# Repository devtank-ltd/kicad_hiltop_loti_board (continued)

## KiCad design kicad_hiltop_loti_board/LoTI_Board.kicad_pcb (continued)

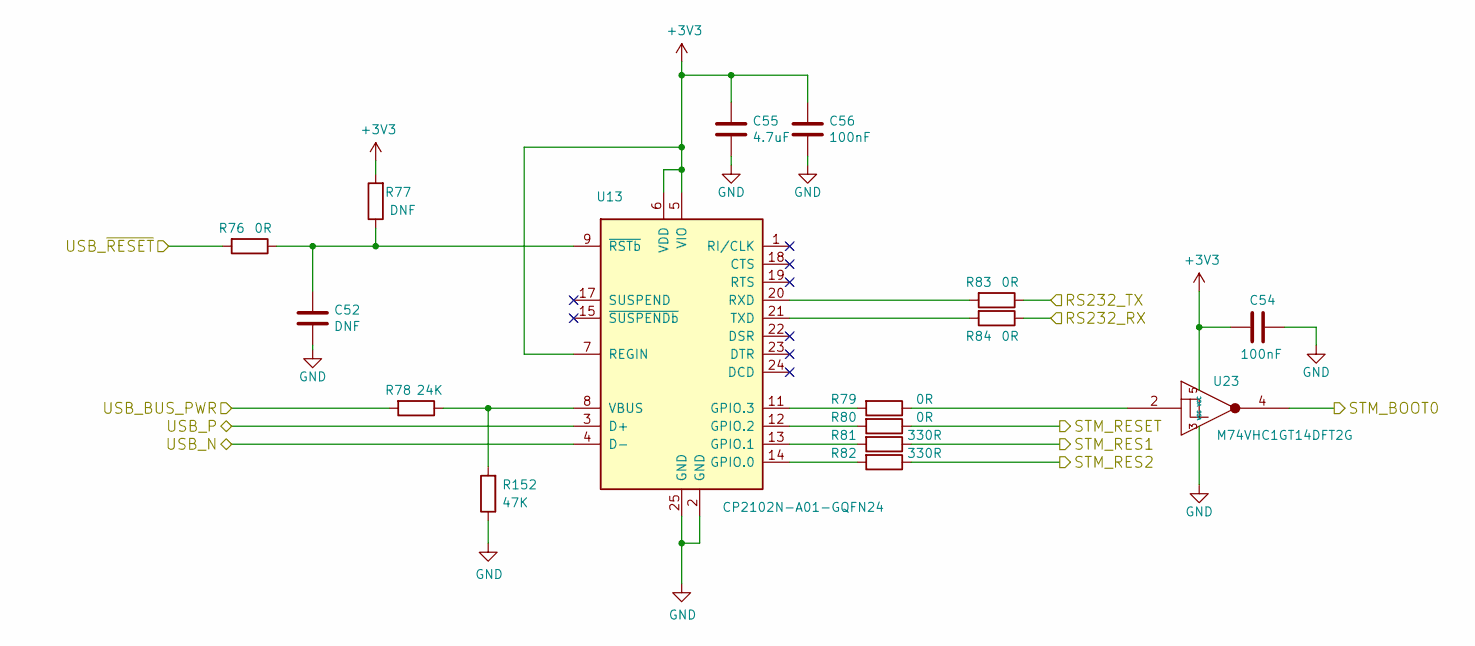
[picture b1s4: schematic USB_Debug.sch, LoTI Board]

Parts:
C52: DNF; C_0603_1608Metric
C54, C56: 100nF; C_0603_1608Metric
C55: 4.7uF; C_0805_2012Metric
R76, R79, R80, R83, R84: 0R; R_0603_1608Metric
R77: DNF; R_0603_1608Metric
R78: 24K; R_0603_1608Metric
R81, R82: 330R; R_0603_1608Metric
R152: 47K; R_0603_1608Metric
U13: CP2102N-A01-GQFN24; QFN-24-1EP_4x4mm_P0.5mm_EP2.6x2.6mm_ThermalVias
U23: M74VHC1GT14DFT2G; SOT-353_SC-70-5

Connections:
+3V3: C54.2, C55.1, C56.1, R77.2, U13.5 (VIO), U13.6 (VDD), U13.7 (REGIN), U23.5 (VCC); also elsewhere on the board
+5V: R78.2; also elsewhere on the board
/RESET: R76.2; also elsewhere on the board
/STM_BOOT0: U23.4; also elsewhere on the board
/STM_DEBUG_RX: R84.1; also elsewhere on the board
/STM_DEBUG_TX: R83.1; also elsewhere on the board
/STM_RES1: R81.1; also elsewhere on the board
/STM_RES2: R82.1; also elsewhere on the board
/STM_RESET: R80.1; also elsewhere on the board
/USB_DEBUG_N: U13.4 (D-); also elsewhere on the board
/USB_DEBUG_P: U13.3 (D+); also elsewhere on the board
GND: C52.2, C54.1, C55.2, C56.2, R152.1, U13.2 (GND), U13.25 (GND), U23.3 (VSS); also elsewhere on the board
unnamed: C52.1, R76.1, R77.1, U13.9 (~RSTb)
unnamed: R79.1, U23.2
unnamed: R79.2, U13.11 (GPIO.3)
unnamed: R80.2, U13.12 (GPIO.2)
unnamed: R81.2, U13.13 (GPIO.1)
unnamed: R82.2, U13.14 (GPIO.0)
unnamed: R83.2, U13.20 (RXD)
unnamed: R84.2, U13.21 (TXD)
unnamed: R78.1, R152.2, U13.8 (VBUS)

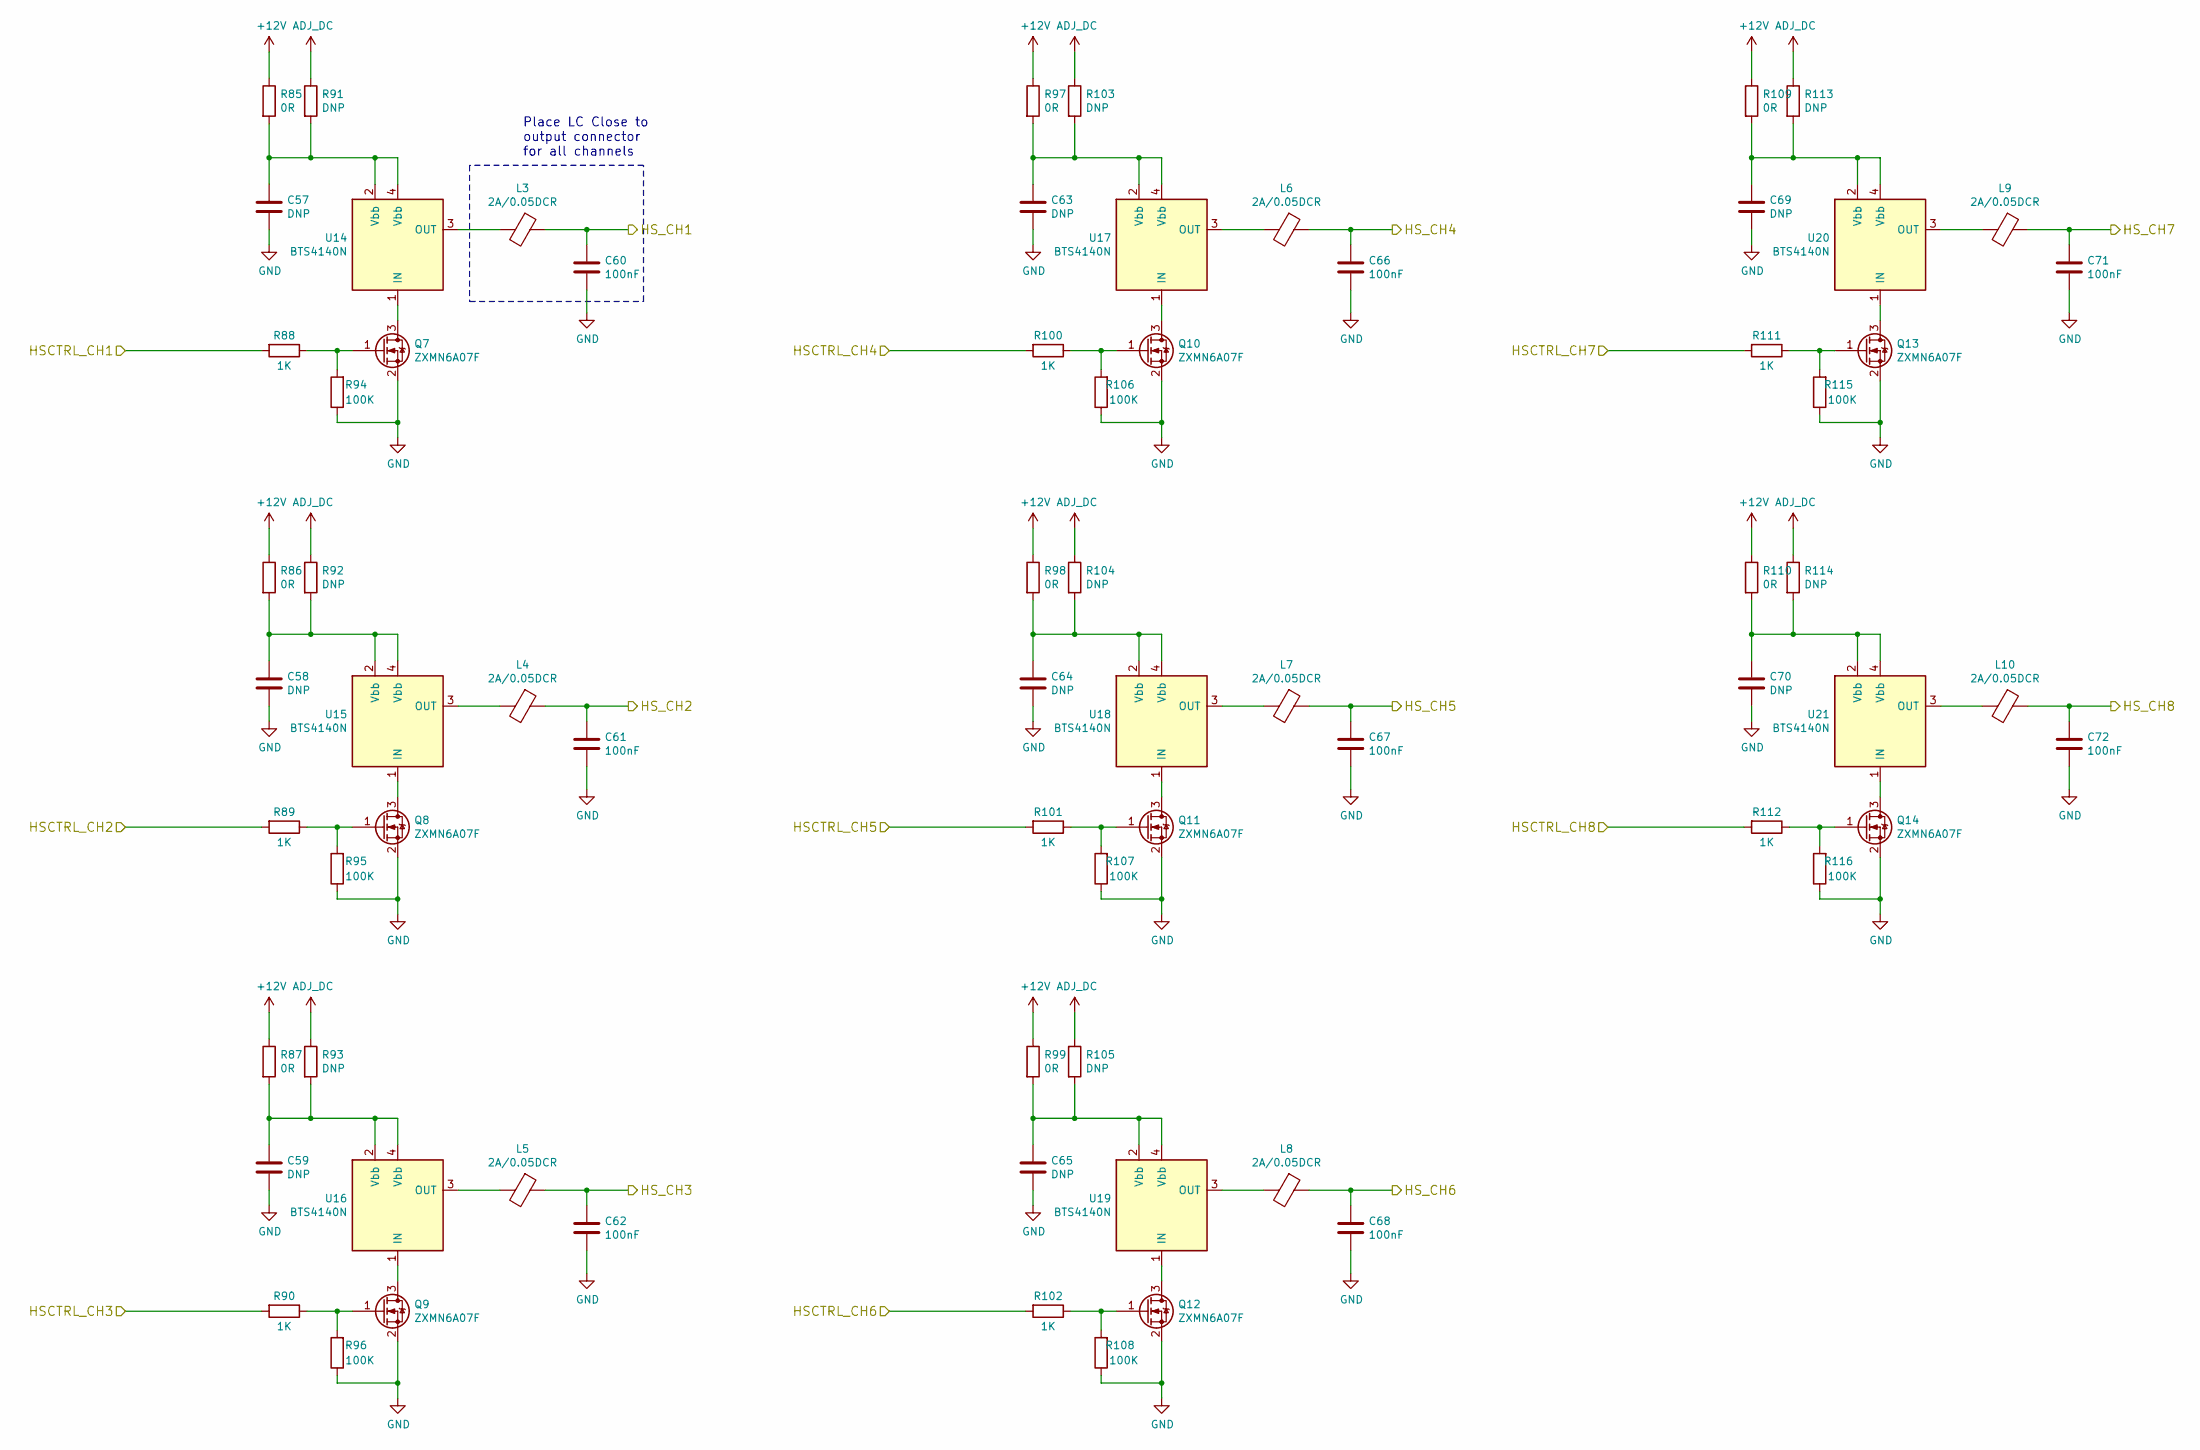
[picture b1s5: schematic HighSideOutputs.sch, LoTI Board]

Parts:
C57, C58, C59, C63, C64, C65, C69, C70: DNP; C_0805_2012Metric
C60, C61, C62, C66, C67, C68, C71, C72: 100nF; C_0402_1005Metric
L3, L4, L5, L6, L7, L8, L9, L10: 2A/0.05DCR; L_0805_2012Metric
Q7, Q8, Q9, Q10, Q11, Q12, Q13, Q14: ZXMN6A07F; SOT-23
R85, R86, R87, R97, R98, R99, R109, R110: 0R; R_0805_2012Metric
R88, R89, R90, R100, R101, R102, R111, R112: 1K; R_0603_1608Metric
R91, R92, R93, R103, R104, R105, R113, R114: DNP; R_0805_2012Metric
R94, R95, R96, R106, R107, R108, R115, R116: 100K; R_0603_1608Metric
U14, U15, U16, U17, U18, U19, U20, U21: BTS4140N; SOT-223

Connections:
+12V: R85.1, R86.1, R87.1, R97.1, R98.1, R99.1, R109.1, R110.1; also elsewhere on the board
/HS_CTRL_SW1: R88.2; also elsewhere on the board
/HS_CTRL_SW2: R89.2; also elsewhere on the board
/HS_CTRL_SW3: R90.2; also elsewhere on the board
/HS_CTRL_SW4: R100.2; also elsewhere on the board
/HS_CTRL_SW5: R101.2; also elsewhere on the board
/HS_CTRL_SW6: R102.2; also elsewhere on the board
/HS_CTRL_SW7: R111.2; also elsewhere on the board
/HS_CTRL_SW8: R112.2; also elsewhere on the board
/HS_OUT1: C60.1, L3.1; also elsewhere on the board
/HS_OUT2: C61.1, L4.1; also elsewhere on the board
/HS_OUT3: C62.1, L5.1; also elsewhere on the board
/HS_OUT4: C66.1, L6.1; also elsewhere on the board
/HS_OUT5: C67.1, L7.1; also elsewhere on the board
/HS_OUT6: C68.1, L8.1; also elsewhere on the board
/HS_OUT7: C71.1, L9.1; also elsewhere on the board
/HS_OUT8: C72.1, L10.1; also elsewhere on the board
ADJ_DC: R91.1, R92.1, R93.1, R103.1, R104.1, R105.1, R113.1, R114.1; also elsewhere on the board
GND: C57.2, C58.2, C59.2, C60.2, C61.2, C62.2, C63.2, C64.2, C65.2, C66.2, C67.2, C68.2, C69.2, C70.2, C71.2, C72.2, Q7.2 (S), Q8.2 (S), Q9.2 (S), Q10.2 (S), Q11.2 (S), Q12.2 (S), Q13.2 (S), Q14.2 (S), R94.1, R95.1, R96.1, R106.1, R107.1, R108.1, R115.1, R116.1; also elsewhere on the board
unnamed: C57.1, R85.2, R91.2, U14.2 (Vbb), U14.4 (Vbb)
unnamed: C58.1, R86.2, R92.2, U15.2 (Vbb), U15.4 (Vbb)
unnamed: C59.1, R87.2, R93.2, U16.2 (Vbb), U16.4 (Vbb)
unnamed: C63.1, R97.2, R103.2, U17.2 (Vbb), U17.4 (Vbb)
unnamed: C64.1, R98.2, R104.2, U18.2 (Vbb), U18.4 (Vbb)
unnamed: C65.1, R99.2, R105.2, U19.2 (Vbb), U19.4 (Vbb)
unnamed: C69.1, R109.2, R113.2, U20.2 (Vbb), U20.4 (Vbb)
unnamed: C70.1, R110.2, R114.2, U21.2 (Vbb), U21.4 (Vbb)
unnamed: L3.2, U14.3 (OUT)
unnamed: L4.2, U15.3 (OUT)
unnamed: L5.2, U16.3 (OUT)
unnamed: L6.2, U17.3 (OUT)
unnamed: L7.2, U18.3 (OUT)
unnamed: L8.2, U19.3 (OUT)
unnamed: L9.2, U20.3 (OUT)
unnamed: L10.2, U21.3 (OUT)
unnamed: Q7.1 (G), R88.1, R94.2
unnamed: Q7.3 (D), U14.1 (IN)
unnamed: Q8.1 (G), R89.1, R95.2
unnamed: Q8.3 (D), U15.1 (IN)
unnamed: Q9.1 (G), R90.1, R96.2
unnamed: Q9.3 (D), U16.1 (IN)
unnamed: Q10.1 (G), R100.1, R106.2
unnamed: Q10.3 (D), U17.1 (IN)
unnamed: Q11.1 (G), R101.1, R107.2
unnamed: Q11.3 (D), U18.1 (IN)
unnamed: Q12.1 (G), R102.1, R108.2
unnamed: Q12.3 (D), U19.1 (IN)
unnamed: Q13.1 (G), R111.1, R115.2
unnamed: Q13.3 (D), U20.1 (IN)
unnamed: Q14.1 (G), R112.1, R116.2
unnamed: Q14.3 (D), U21.1 (IN)

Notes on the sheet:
Place LC Close to output connector for all channels

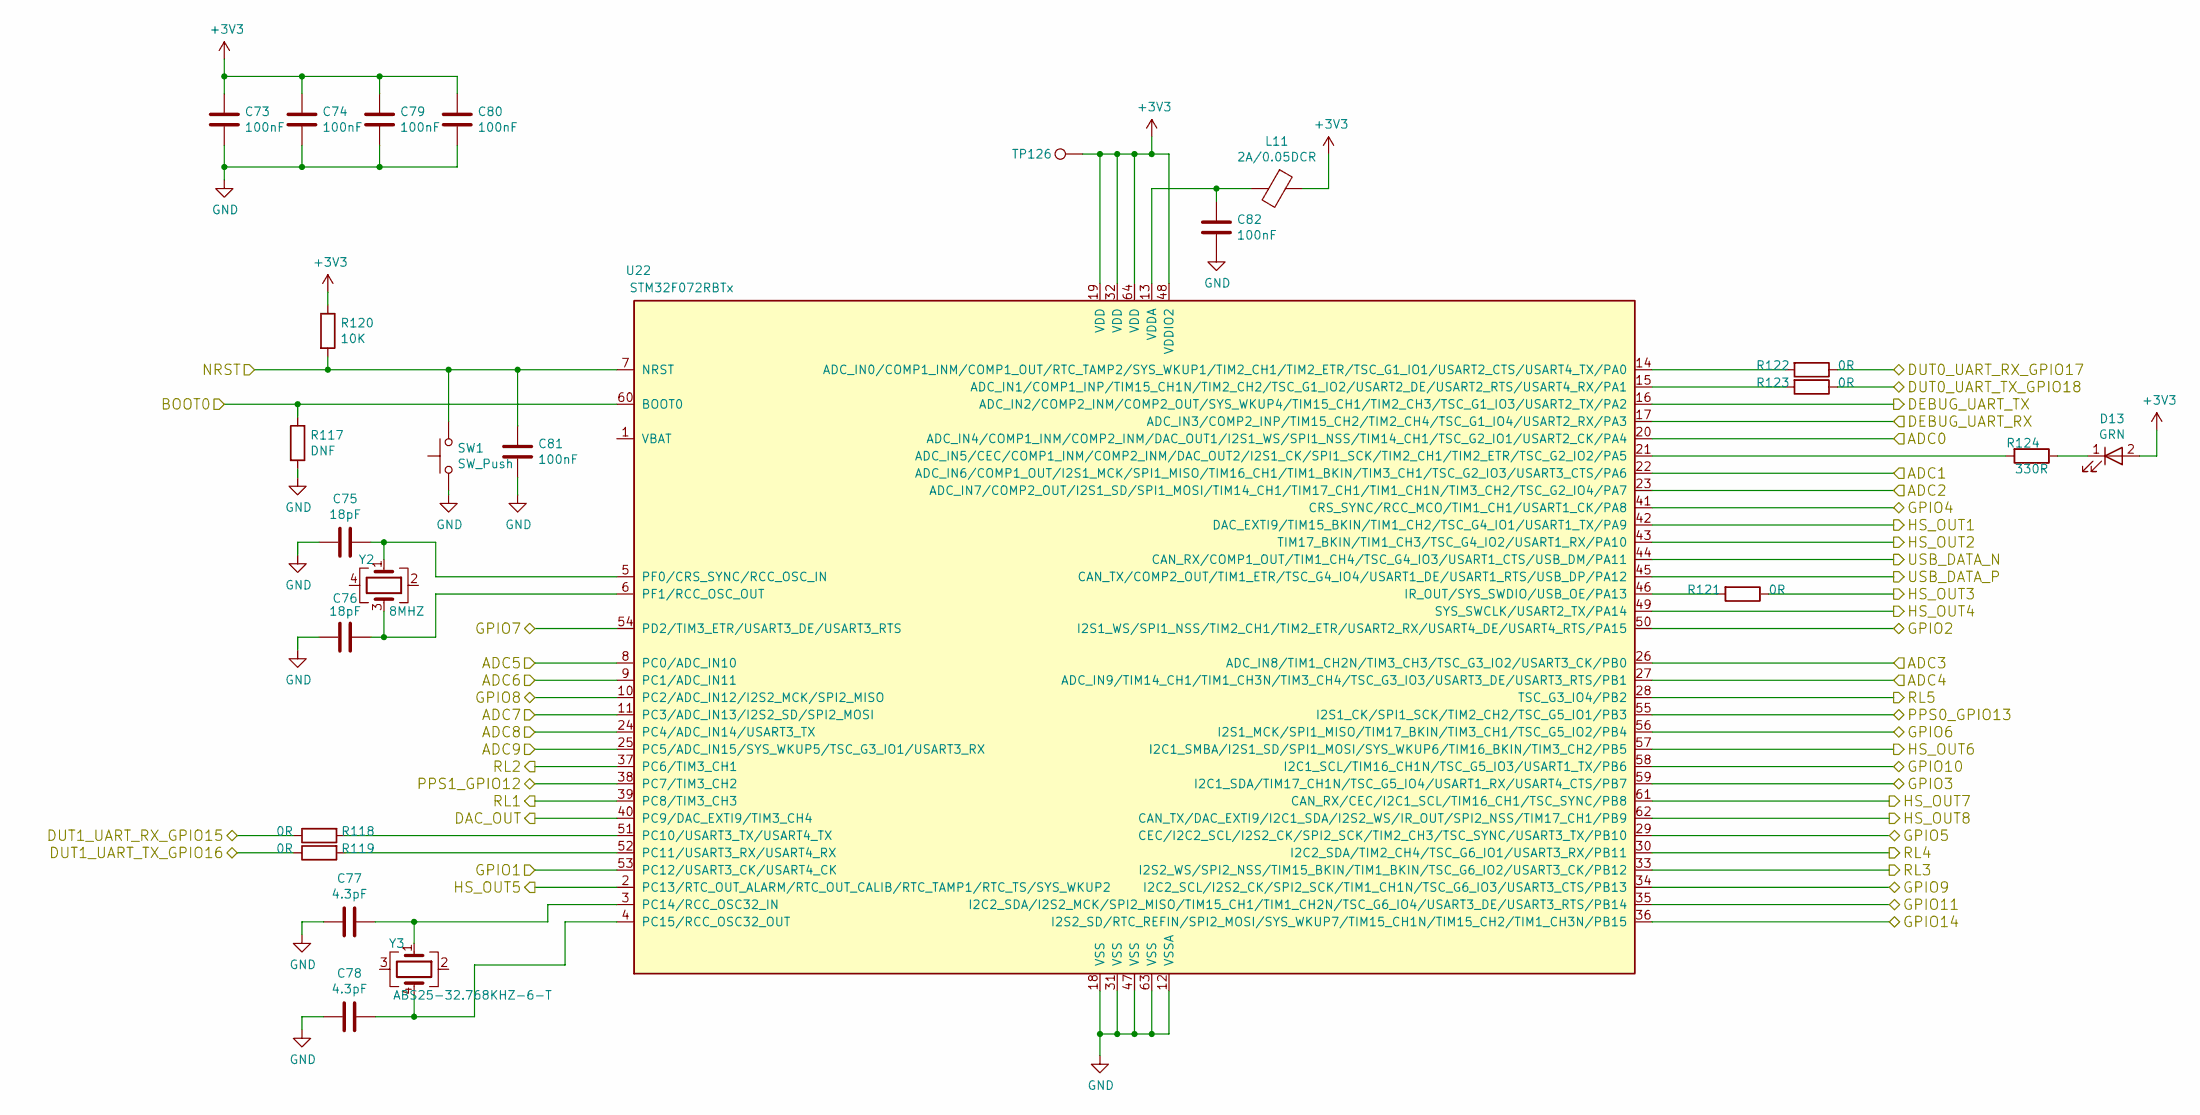
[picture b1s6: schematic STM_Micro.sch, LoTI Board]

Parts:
C73, C74, C79, C80, C81, C82: 100nF; C_0603_1608Metric
C75, C76: 18pF; C_0603_1608Metric
C77, C78: 4.3pF; C_0603_1608Metric
D13: GRN; LED_0603_1608Metric
L11: 2A/0.05DCR; L_0805_2012Metric
R117: DNF; R_0603_1608Metric
R118, R119, R121, R122, R123: 0R; R_0603_1608Metric
R120: 10K; R_0603_1608Metric
R124: 330R; R_0603_1608Metric
SW1: SW_Push; SW_SPST_B3U-1000P
TP126: Test_Point; TestPoint_THTPad_D1.0mm_Drill0.5mm
U22: STM32F072RBTx; LQFP-64_10x10mm_P0.5mm
Y2: 8MHZ; Crystal_SMD_Abracon_ABM3C-4Pin_5.0x3.2mm
Y3: ABS25-32.768KHZ-6-T; Crystal_SMD_7050-4Pin_7.0x5.0mm

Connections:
+3V3: C73.1, C74.1, C79.1, C80.1, D13.2 (A), L11.1, R120.1, TP126.1, U22.19 (VDD), U22.32 (VDD), U22.48 (VDDIO2), U22.64 (VDD); also elsewhere on the board
/ADC0: U22.20 (ADC_IN4/COMP1_INM/COMP2_INM/DAC_OUT1/I2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); also elsewhere on the board
/ADC1: U22.22 (ADC_IN6/COMP1_OUT/I2S1_MCK/SPI1_MISO/TI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); also elsewhere on the board
/ADC2: U22.23 (ADC_IN7/COMP2_OUT/I2S1_SD/SPI1_MOSI/TIM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); also elsewhere on the board
/ADC3: U22.26 (ADC_IN8/TIM1_CH2N/TIM3_CH3/TSC_G3_IO2/U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); also elsewhere on the board
/ADC4: U22.27 (ADC_IN9/TIM14_CH1/TIM1_CH3N/TIM3_CH4/TS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); also elsewhere on the board
/ADC5: U22.8 (PC0/ADC_IN10); also elsewhere on the board
/ADC6: U22.9 (PC1/ADC_IN11); also elsewhere on the board
/ADC7: U22.11 (PC3/ADC_IN13/I2S2_SD/SPI2_MOSI); also elsewhere on the board
/ADC8: U22.24 (PC4/ADC_IN14/USART3_TX); also elsewhere on the board
/ADC9: U22.25 (PC5/ADC_IN15/SYS_WKUP5/TSC_G3_IO1/USART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); also elsewhere on the board
/DUT0_UART_RX_GPIO17: R122.1; also elsewhere on the board
/DUT0_UART_TX_GPIO18: R123.1; also elsewhere on the board
/DUT1_UART_RX_GPIO15: R118.1; also elsewhere on the board
/DUT1_UART_TX_GPIO16: R119.1; also elsewhere on the board
/GPIO1: U22.53 (PC12/USART3_CK/USART4_CK); also elsewhere on the board
/GPIO2: U22.50 (I2S1_WS/SPI1_NSS/TIM2_CH1/TIM2_ETR/USAR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); also elsewhere on the board
/GPIO3: U22.59 (I2C1_SDA/TIM17_CH1N/TSC_G5_IO4/USART1_R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); also elsewhere on the board
/GPIO4: U22.41 (CRS_SYNC/RCC_MCO/TIM1_CH1/USART1_CK/PA8); also elsewhere on the board
/GPIO5: U22.29 (CEC/I2C2_SCL/I2S2_CK/SPI2_SCK/TIM2_CH3/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); also elsewhere on the board
/GPIO6: U22.56 (I2S1_MCK/SPI1_MISO/TIM17_BKIN/TIM3_CH1/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); also elsewhere on the board
/GPIO7: U22.54 (PD2/TIM3_ETR/USART3_DE/USART3_RTS); also elsewhere on the board
/GPIO8: U22.10 (PC2/ADC_IN12/I2S2_MCK/SPI2_MISO); also elsewhere on the board
/GPIO9: U22.34 (I2C2_SCL/I2S2_CK/SPI2_SCK/TIM1_CH1N/TSC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); also elsewhere on the board
/GPIO10: U22.58 (I2C1_SCL/TIM16_CH1N/TSC_G5_IO3/USART1_T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); also elsewhere on the board
/GPIO11: U22.35 (I2C2_SDA/I2S2_MCK/SPI2_MISO/TIM15_CH1/T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); also elsewhere on the board
/GPIO14: U22.36 (I2S2_SD/RTC_REFIN/SPI2_MOSI/SYS_WKUP7/T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); also elsewhere on the board
/HS_CTRL_SW1: U22.42 (DAC_EXTI9/TIM15_BKIN/TIM1_CH2/TSC_G4_IO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); also elsewhere on the board
/HS_CTRL_SW2: U22.43 (TIM17_BKIN/TIM1_CH3/TSC_G4_IO2/USART1_R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); also elsewhere on the board
/HS_CTRL_SW3: R121.1; also elsewhere on the board
/HS_CTRL_SW4: U22.49 (SYS_SWCLK/USART2_TX/PA14); also elsewhere on the board
/HS_CTRL_SW5: U22.2 (PC13/RTC_OUT_ALARM/RTC_OUT_CALIB/RTC_TA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); also elsewhere on the board
/HS_CTRL_SW6: U22.57 (I2C1_SMBA/I2S1_SD/SPI1_MOSI/SYS_WKUP6/T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); also elsewhere on the board
/HS_CTRL_SW7: U22.61 (CAN_RX/CEC/I2C1_SCL/TIM16_CH1/TSC_SYNC/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); also elsewhere on the board
/HS_CTRL_SW8: U22.62 (CAN_TX/DAC_EXTI9/I2C1_SDA/I2S2_WS/IR_OU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); also elsewhere on the board
/PPS0_GPIO13: U22.55 (I2S1_CK/SPI1_SCK/TIM2_CH2/TSC_G5_IO1/PB3); also elsewhere on the board
/PPS1_GPIO12: U22.38 (PC7/TIM3_CH2); also elsewhere on the board
/RL1_OUT: U22.39 (PC8/TIM3_CH3); also elsewhere on the board
/RL2_OUT: U22.37 (PC6/TIM3_CH1); also elsewhere on the board
/RL3_OUT: U22.33 (I2S2_WS/SPI2_NSS/TIM15_BKIN/TIM1_BKIN/T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); also elsewhere on the board
/RL4_OUT: U22.30 (I2C2_SDA/TIM2_CH4/TSC_G6_IO1/USART3_RX/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); also elsewhere on the board
/RL5_OUT: U22.28 (TSC_G3_IO4/PB2); also elsewhere on the board
/STM_BOOT0: R117.1, U22.60 (BOOT0); also elsewhere on the board
/STM_DEBUG_RX: U22.17 (ADC_IN3/COMP2_INP/TIM15_CH2/TIM2_CH4/TS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); also elsewhere on the board
/STM_DEBUG_TX: U22.16 (ADC_IN2/COMP2_INM/COMP2_OUT/SYS_WKUP4/T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); also elsewhere on the board
/STM_Micro/DAC_OUT: U22.40 (PC9/DAC_EXTI9/TIM3_CH4); also elsewhere on the board
/STM_RESET: C81.1, R120.2, SW1.2, U22.7 (NRST); also elsewhere on the board
/USB_DATA_N: U22.44 (CAN_RX/COMP1_OUT/TIM1_CH4/TSC_G4_IO3/US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); also elsewhere on the board
/USB_DATA_P: U22.45 (CAN_TX/COMP2_OUT/TIM1_ETR/TSC_G4_IO4/US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); also elsewhere on the board
GND: C73.2, C74.2, C75.2, C76.2, C77.2, C78.2, C79.2, C80.2, C81.2, C82.2, R117.2, SW1.1, U22.12 (VSSA), U22.18 (VSS), U22.31 (VSS), U22.47 (VSS), U22.63 (VSS); also elsewhere on the board
unnamed: C75.1, U22.5 (PF0/CRS_SYNC/RCC_OSC_IN), Y2.1
unnamed: C76.1, U22.6 (PF1/RCC_OSC_OUT), Y2.3
unnamed: C77.1, U22.3 (PC14/RCC_OSC32_IN), Y3.1
unnamed: C78.1, U22.4 (PC15/RCC_OSC32_OUT), Y3.4
unnamed: C82.1, L11.2, U22.13 (VDDA)
unnamed: D13.1 (K), R124.1
unnamed: R118.2, U22.51 (PC10/USART3_TX/USART4_TX)
unnamed: R119.2, U22.52 (PC11/USART3_RX/USART4_RX)
unnamed: R121.2, U22.46 (IR_OUT/SYS_SWDIO/USB_OE/PA13)
unnamed: R122.2, U22.14 (ADC_IN0/COMP1_INM/COMP1_OUT/RTC_TAMP2/S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)
unnamed: R123.2, U22.15 (ADC_IN1/COMP1_INP/TIM15_CH1N/TIM2_CH2/T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)
unnamed: R124.2, U22.21 (ADC_IN5/CEC/COMP1_INM/COMP2_INM/DAC_OUT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)

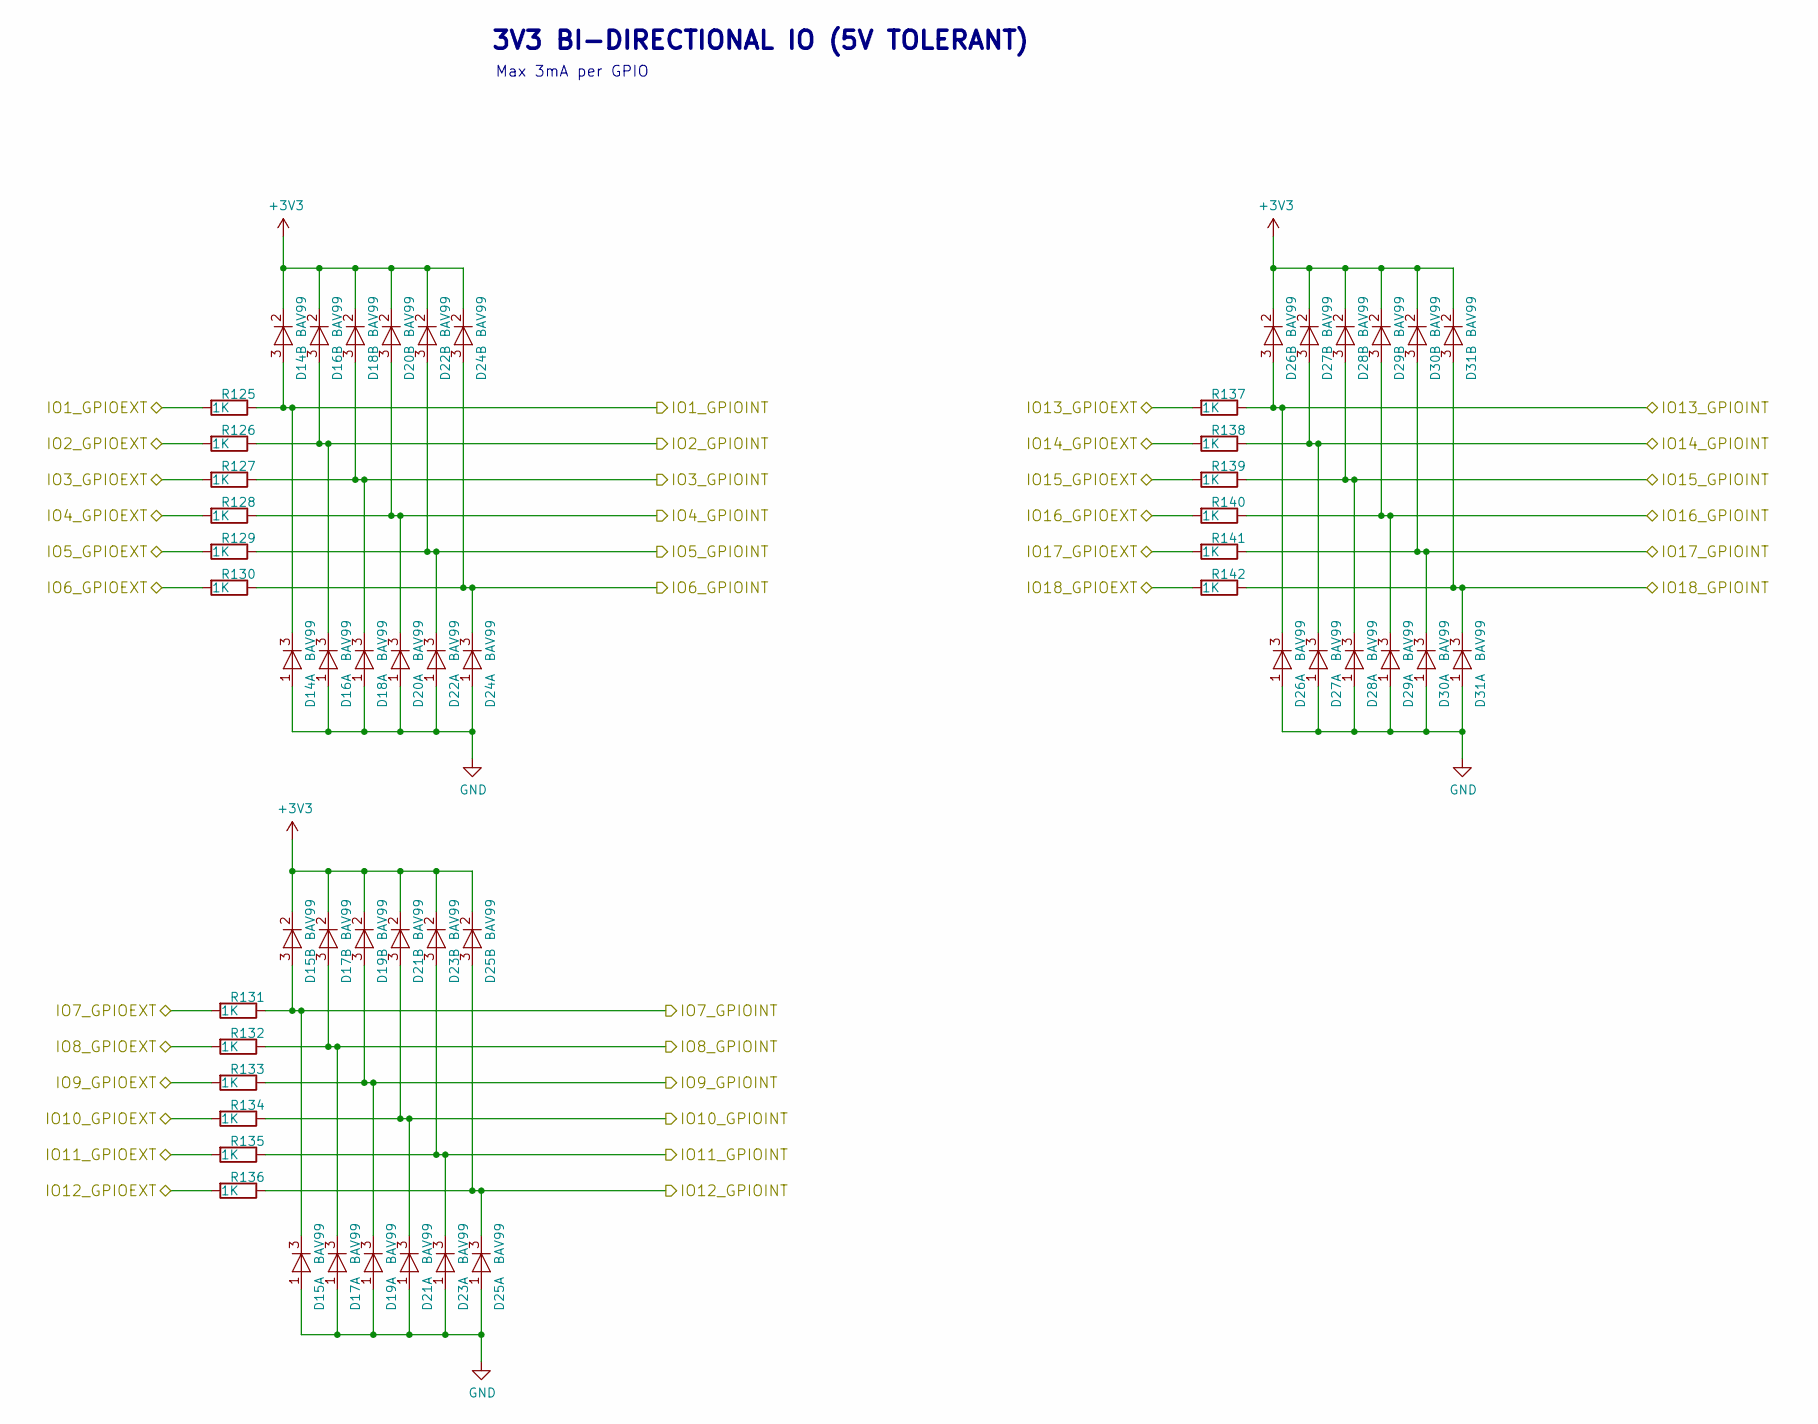
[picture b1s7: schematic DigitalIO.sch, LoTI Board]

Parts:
D14, D15, D16, D17, D18, D19, D20, D21, D22, D23, D24, D25, D26, D27, D28, D29, D30, D31: BAV99; SOT-23
R125, R126, R127, R128, R129, R130, R131, R132, R133, R134, R135, R136, R137, R138, R139, R140, R141, R142: 1K; R_0603_1608Metric

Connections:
+3V3: D14.2 (K), D15.2 (K), D16.2 (K), D17.2 (K), D18.2 (K), D19.2 (K), D20.2 (K), D21.2 (K), D22.2 (K), D23.2 (K), D24.2 (K), D25.2 (K), D26.2 (K), D27.2 (K), D28.2 (K), D29.2 (K), D30.2 (K), D31.2 (K); also elsewhere on the board
/DUT0_RX_GPIO17_EXT: R141.2; also elsewhere on the board
/DUT0_TX_GPIO18_EXT: R142.2; also elsewhere on the board
/DUT0_UART_RX_GPIO17: D30.3 (K), R141.1; also elsewhere on the board
/DUT0_UART_TX_GPIO18: D31.3 (K), R142.1; also elsewhere on the board
/DUT1_RX_GPIO15_EXT: R139.2; also elsewhere on the board
/DUT1_TX_GPIO16_EXT: R140.2; also elsewhere on the board
/DUT1_UART_RX_GPIO15: D28.3 (K), R139.1; also elsewhere on the board
/DUT1_UART_TX_GPIO16: D29.3 (K), R140.1; also elsewhere on the board
/GPIO1: D14.3 (K), R125.1; also elsewhere on the board
/GPIO1_EXT: R125.2; also elsewhere on the board
/GPIO2: D16.3 (K), R126.1; also elsewhere on the board
/GPIO2_EXT: R126.2; also elsewhere on the board
/GPIO3: D18.3 (K), R127.1; also elsewhere on the board
/GPIO3_EXT: R127.2; also elsewhere on the board
/GPIO4: D20.3 (K), R128.1; also elsewhere on the board
/GPIO4_EXT: R128.2; also elsewhere on the board
/GPIO5: D22.3 (K), R129.1; also elsewhere on the board
/GPIO5_EXT: R129.2; also elsewhere on the board
/GPIO6: D24.3 (K), R130.1; also elsewhere on the board
/GPIO6_EXT: R130.2; also elsewhere on the board
/GPIO7: D15.3 (K), R131.1; also elsewhere on the board
/GPIO7_EXT: R131.2; also elsewhere on the board
/GPIO8: D17.3 (K), R132.1; also elsewhere on the board
/GPIO8_EXT: R132.2; also elsewhere on the board
/GPIO9: D19.3 (K), R133.1; also elsewhere on the board
/GPIO9_EXT: R133.2; also elsewhere on the board
/GPIO10: D21.3 (K), R134.1; also elsewhere on the board
/GPIO10_EXT: R134.2; also elsewhere on the board
/GPIO11: D23.3 (K), R135.1; also elsewhere on the board
/GPIO11_EXT: R135.2; also elsewhere on the board
/GPIO14: D27.3 (K), R138.1; also elsewhere on the board
/GPIO14_EXT: R138.2; also elsewhere on the board
/PPS0_GPIO13: D26.3 (K), R137.1; also elsewhere on the board
/PPS0_GPIO13_EXT: R137.2; also elsewhere on the board
/PPS1_GPIO12: D25.3 (K), R136.1; also elsewhere on the board
/PPS1_GPIO12_EXT: R136.2; also elsewhere on the board
GND: D14.1 (A), D15.1 (A), D16.1 (A), D17.1 (A), D18.1 (A), D19.1 (A), D20.1 (A), D21.1 (A), D22.1 (A), D23.1 (A), D24.1 (A), D25.1 (A), D26.1 (A), D27.1 (A), D28.1 (A), D29.1 (A), D30.1 (A), D31.1 (A); also elsewhere on the board

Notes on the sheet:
3V3 BI-DIRECTIONAL IO (5V TOLERANT)
Max 3mA per GPIO

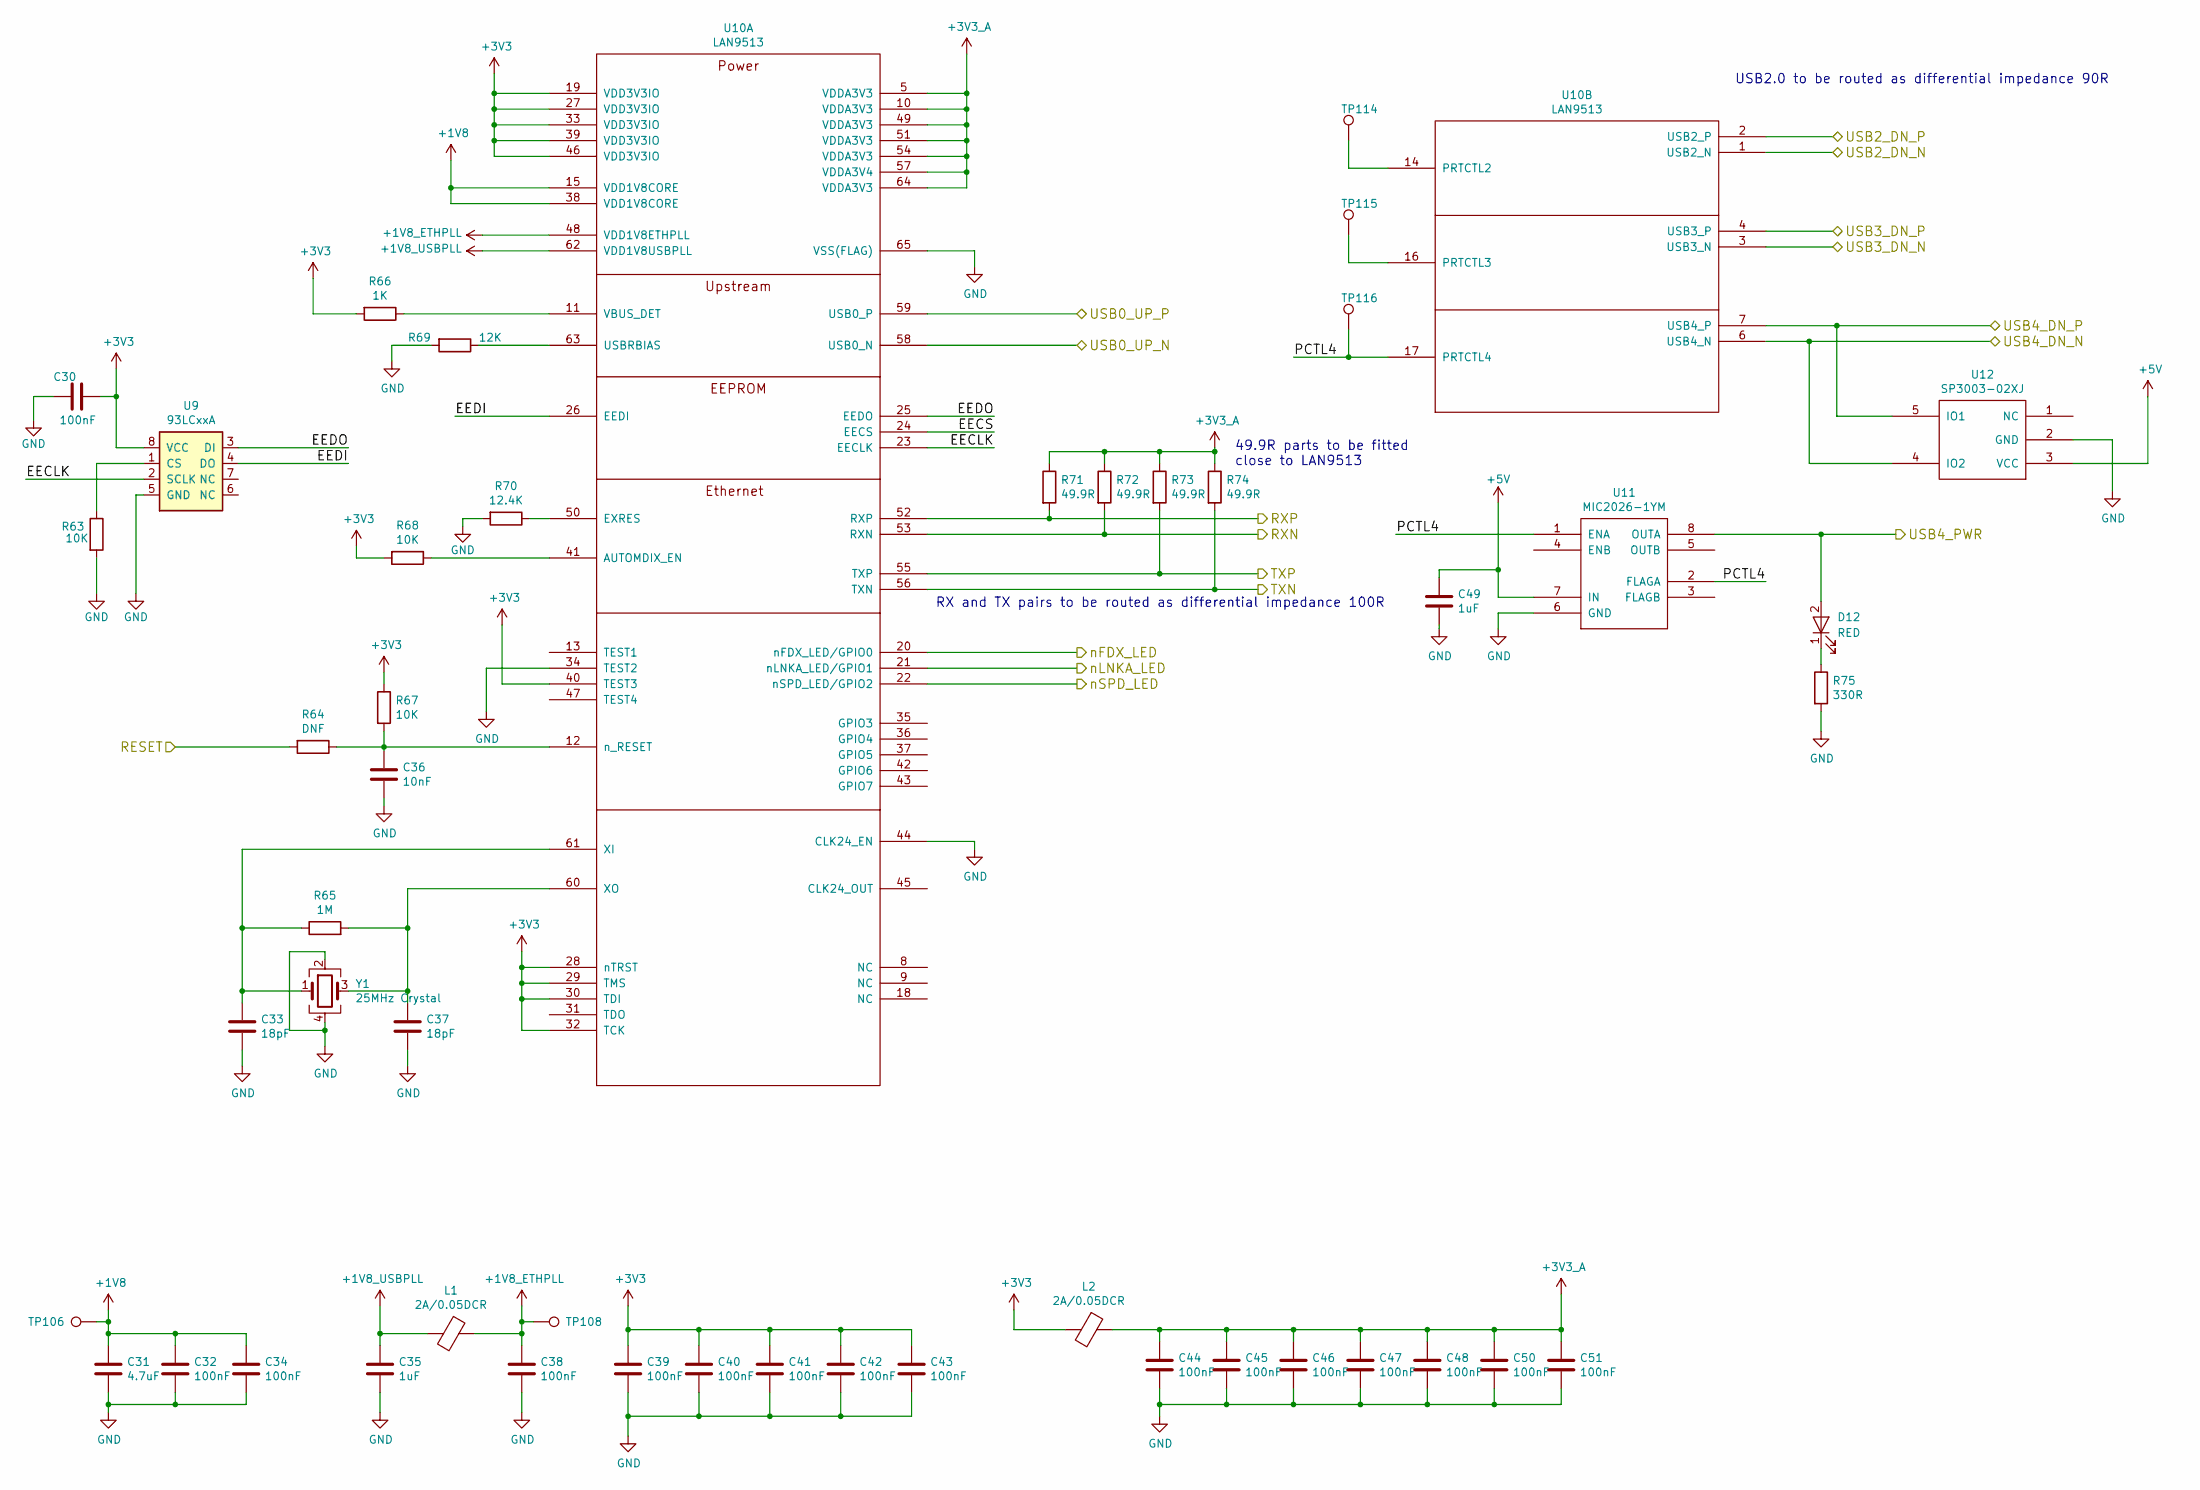
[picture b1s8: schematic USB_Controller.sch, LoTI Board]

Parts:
C30, C32, C34, C39, C40, C41, C42, C43, C44, C45, C46, C47, C48, C50, C51: 100nF; C_0402_1005Metric
C31: 4.7uF; C_0603_1608Metric
C33, C37: 18pF; C_0402_1005Metric
C35, C49: 1uF; C_0603_1608Metric
C36: 10nF; C_0402_1005Metric
C38: 100nF; C_0603_1608Metric
D12: RED; LED_0402_1005Metric
L1, L2: 2A/0.05DCR; L_0805_2012Metric
R63: 10K; R_0603_1608Metric
R64: DNF; R_0603_1608Metric
R65: 1M; R_0402_1005Metric
R66: 1K; R_0402_1005Metric
R67, R68: 10K; R_0402_1005Metric
R69: 12K; R_0402_1005Metric
R70: 12.4K; R_0402_1005Metric
R71, R72, R73, R74: 49.9R; R_0402_1005Metric
R75: 330R; R_0603_1608Metric
TP106, TP108, TP114, TP115, TP116: Test_Point; TestPoint_THTPad_D1.0mm_Drill0.5mm
U9: 93LCxxA; SOIC-8_3.9x4.9mm_P1.27mm
U10: LAN9513; QFN-64-1EP_9x9mm_P0.5mm_EP7.3x7.3mm_ThermalVias
U11: MIC2026-1YM; SOIC-8_3.9x4.9mm_P1.27mm
U12: SP3003-02XJ; SC70-5
Y1: 25MHz Crystal; Crystal_SMD_SeikoEpson_FA238V-4Pin_3.2x2.5mm

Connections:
+1V8: C31.1, C32.1, C34.1, TP106.1, U10.15 (VDD1V8CORE), U10.38 (VDD1V8CORE)
+1V8_ETHPLL: C38.1, L1.1, TP108.1, U10.48 (VDD1V8ETHPLL)
+1V8_USBPLL: C35.1, L1.2, U10.62 (VDD1V8USBPLL)
+3V3: C30.2, C39.1, C40.1, C41.1, C42.1, C43.1, L2.2, R66.2, R67.1, R68.2, U9.8 (VCC), U10.19 (VDD3V3IO), U10.27 (VDD3V3IO), U10.28 (nTRST), U10.29 (TMS), U10.30 (TDI), U10.32 (TCK), U10.33 (VDD3V3IO), U10.39 (VDD3V3IO), U10.40 (TEST3), U10.46 (VDD3V3IO); also elsewhere on the board
+3V3_A: C44.1, C45.1, C46.1, C47.1, C48.1, C50.1, C51.1, L2.1, R71.1, R72.1, R73.1, R74.1, U10.5 (VDDA3V3), U10.10 (VDDA3V3), U10.49 (VDDA3V3), U10.51 (VDDA3V3), U10.54 (VDDA3V3), U10.57 (VDDA3V4), U10.64 (VDDA3V3); also elsewhere on the board
+5V: C49.1, U11.7 (IN), U12.3 (VCC); also elsewhere on the board
/RESET: R64.2; also elsewhere on the board
/RXN: R72.2, U10.53 (RXN); also elsewhere on the board
/RXP: R71.2, U10.52 (RXP); also elsewhere on the board
/TXN: R74.2, U10.56 (TXN); also elsewhere on the board
/TXP: R73.2, U10.55 (TXP); also elsewhere on the board
/USB_AUX_N: U10.6 (USB4_N), U12.4 (IO2); also elsewhere on the board
/USB_AUX_P: U10.7 (USB4_P), U12.5 (IO1); also elsewhere on the board
/USB_AUX_PWR: D12.2 (A), U11.8 (OUTA); also elsewhere on the board
/USB_Controller/EECLK: U9.2 (SCLK), U10.23 (EECLK)
/USB_Controller/EECS: U10.24 (EECS)
/USB_Controller/EEDI: U9.4 (DO), U10.26 (EEDI)
/USB_Controller/EEDO: U9.3 (DI), U10.25 (EEDO)
/USB_Controller/PCTL4: TP116.1, U10.17 (PRTCTL4), U11.1 (ENA), U11.2 (FLAGA)
/USB_DATA_N: U10.1 (USB2_N); also elsewhere on the board
/USB_DATA_P: U10.2 (USB2_P); also elsewhere on the board
/USB_DEBUG_N: U10.3 (USB3_N); also elsewhere on the board
/USB_DEBUG_P: U10.4 (USB3_P); also elsewhere on the board
/USB_ROOT_N: U10.58 (USB0_N); also elsewhere on the board
/USB_ROOT_P: U10.59 (USB0_P); also elsewhere on the board
/nFDX_LED: U10.20 (nFDX_LED/GPIO0); also elsewhere on the board
/nLNKA_LED: U10.21 (nLNKA_LED/GPIO1); also elsewhere on the board
/nSPD_LED: U10.22 (nSPD_LED/GPIO2); also elsewhere on the board
GND: C30.1, C31.2, C32.2, C33.2, C34.2, C35.2, C36.2, C37.2, C38.2, C39.2, C40.2, C41.2, C42.2, C43.2, C44.2, C45.2, C46.2, C47.2, C48.2, C49.2, C50.2, C51.2, R63.2, R69.2, R70.2, R75.2, U9.5 (GND), U10.34 (TEST2), U10.44 (CLK24_EN), U10.65 (VSS(FLAG)), U11.6 (GND), U12.2 (GND), Y1.2, Y1.4; also elsewhere on the board
unnamed: C33.1, R65.1, U10.61 (XI), Y1.1
unnamed: C36.1, R64.1, R67.2, U10.12 (n_RESET)
unnamed: C37.1, R65.2, U10.60 (XO), Y1.3
unnamed: D12.1 (K), R75.1
unnamed: R63.1, U9.1 (CS)
unnamed: R66.1, U10.11 (VBUS_DET)
unnamed: R68.1, U10.41 (AUTOMDIX_EN)
unnamed: R69.1, U10.63 (USBRBIAS)
unnamed: R70.1, U10.50 (EXRES)
unnamed: TP114.1, U10.14 (PRTCTL2)
unnamed: TP115.1, U10.16 (PRTCTL3)

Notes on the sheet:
49.9R parts to be fitted close to LAN9513
RX and TX pairs to be routed as differential impedance 100R
USB2.0 to be routed as differential impedance 90R
